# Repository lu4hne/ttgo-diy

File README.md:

# ttgo-diy
Create your ttgo lora with parts.

Two models of plates to assemble a ttgo in long format, With its elements one after another.
Or the mini version, with the esp32 on the back side Lora, and oled display on the front.

This project is a copy with discrete components of the ttgo-lora model, focused on those who do not have the possibility of acquiring an original.

# Functions:
The device has a firmware recorded that reports on the web https://sondehub.org/ the detected meteorological probes. Provides information on altitude, temperature, humidity, and very precise coordinates of latitude and longitude.
On the map you can see two states, the one of ascent and descent, changing the color of the globe. At the moment of descent, it calculates the fall zone with an error of less than 100 meters by prediction.

# Setting:
The device is configured with the data of the probe to be tracked, the license of the radio amateur that makes the capture and other data as seen in this video. https://youtu.be/HP3r6paxjF8

# Important:
The probes work in the UHF band between 402Mhz and 405Mhz depending on the probe model and the location where it is launched. This band is not authorized to be used, only weather systems can use them.
Also do not run Probes near the drop zone as it will report false data.

# Español:

Crea tu ttgo lora con piezas.

Dos modelos de placas para montar un ttgo en formato largo, con sus elementos uno tras otro.
O la versión mini, con el esp32 en la parte trasera, Lora y pantalla oled en la parte delantera.

Este proyecto es una copia con componentes discretos del modelo ttgo-lora, enfocado para quienes no tienen la posibilidad de adquirir un original.

# Funcionamiento:
El dispositivo tiene grabado un firmware que informa en la web https://sondehub.org/ las sondas meterologicas detectadas. Brinda información de altitud, temperatura, humedad, y cordenadas muy precisas de latitud y longitud.
En el mapa se pueden observer dos estados, el de ascenso y descenso, cambiando de color el globo. Al momento des descenso calcula por prediccion la zona de caida con un error menor a 100mtrs.

# Configuración:
El dispositivo se configuran los datos de la sonda a rastrear, licencia del radioaficionado que hace la captura y otros datos como se ve en este video. https://youtu.be/HP3r6paxjF8

# Importante:
Las sondas trabahan en la banda de UHF entre 402Mhz y 405Mhz segun el modelo de sonda y la ubicación de donde se lanza. Esta banda no está autorizada para usarse, solo pueden usarlas los sistemas metereologicos.
Tampoco ponga en funcionamiento Sondas cerca de la zona de lanzamiento ya que informaria datos falsos.

#Version mini, doble side

# Video
https://youtube.com/shorts/UzUDJ2xq2zk

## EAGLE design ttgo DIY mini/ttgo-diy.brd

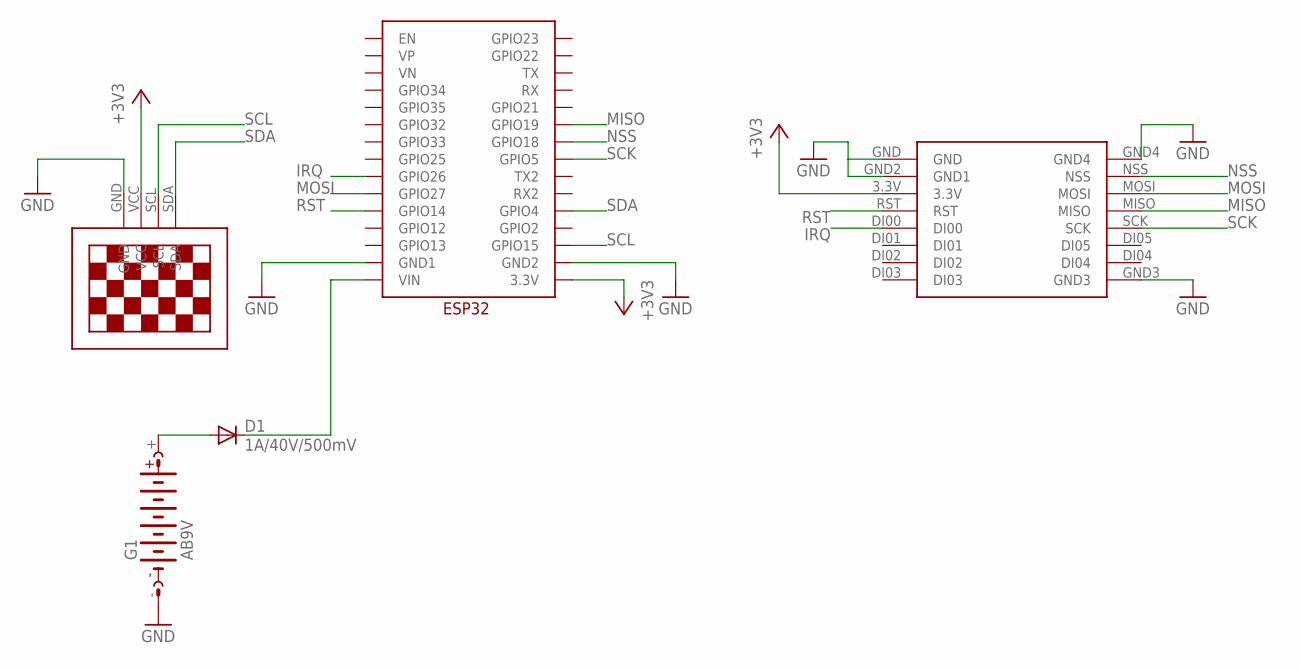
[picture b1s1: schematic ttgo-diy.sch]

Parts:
D1: 1A/40V/500mV; DO35-10
G1: AB9V
U$1: LORA-02DIL; DIL8X11
U$2: ESP32
U$3: 13"OLED13"OLED; 1.3"OLED

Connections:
+3V3: U$1.3.3V, U$2.3.3V, U$3.VCC
GND: G1.-, U$1.GND, U$1.GND2 (GND1), U$1.GND3, U$1.GND4, U$2.GND1, U$2.GND2, U$3.GND
IRQ: U$1.DI00, U$2.GPIO26
MISO: U$1.MISO, U$2.GPIO19
MOSI: U$1.MOSI, U$2.GPIO27
unnamed: D1.C, U$2.VIN
unnamed: D1.A, G1.+
NSS: U$1.NSS, U$2.GPIO18
RST: U$1.RST, U$2.GPIO14
SCK: U$1.SCK, U$2.GPIO5
SCL: U$2.GPIO15, U$3.SCL
SDA: U$2.GPIO4, U$3.SDA

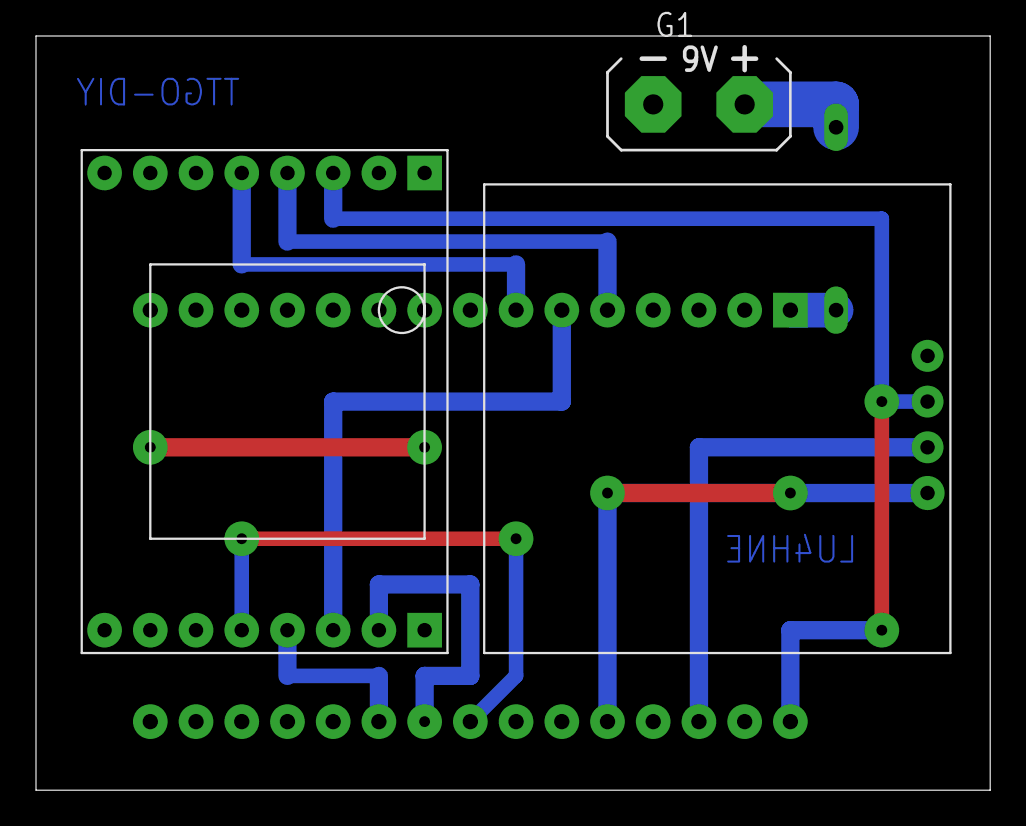
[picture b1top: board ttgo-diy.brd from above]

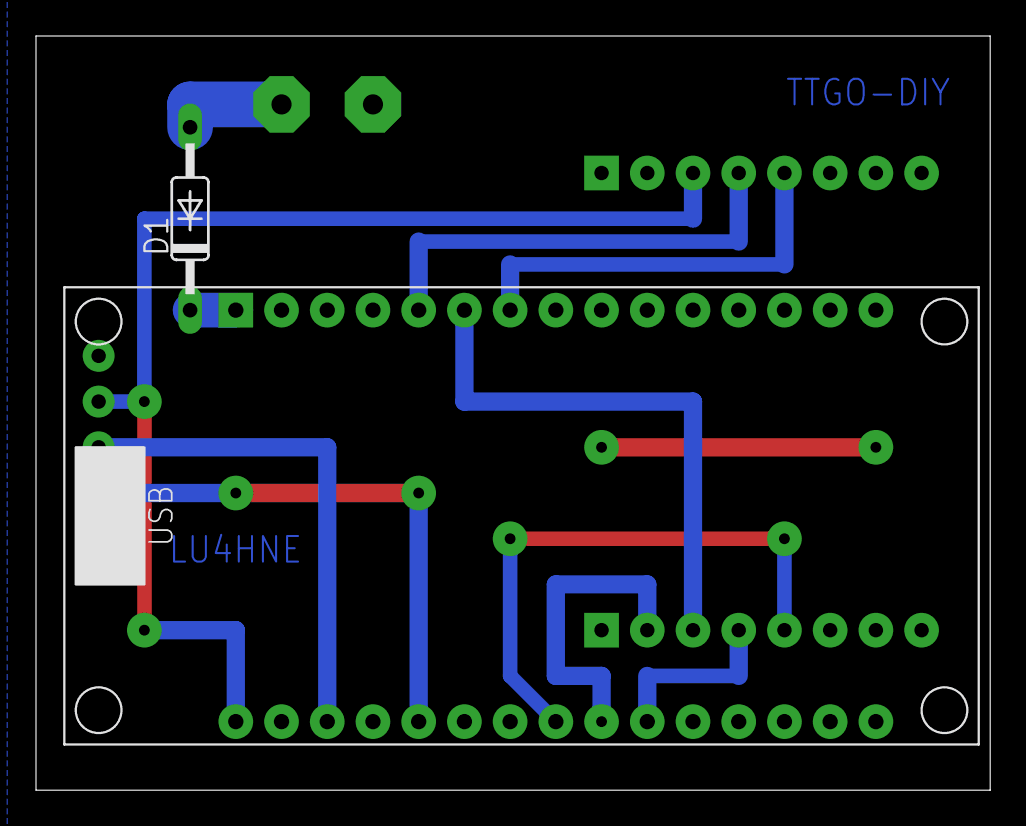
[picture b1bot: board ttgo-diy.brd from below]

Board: 2 copper layers, 53.0 x 41.9 mm, 5 parts (2 on the bottom side), 12 nets.

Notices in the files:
parts and their libraries:
SparkFun-DiscreteSemi: Licensing: Creative Commons ShareAlike 4.0 International - https://creativecommons.org/licenses/by-sa/4.0
